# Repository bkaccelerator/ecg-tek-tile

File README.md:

# ecg-tek-tile
Biorhythm-sensing textile component.

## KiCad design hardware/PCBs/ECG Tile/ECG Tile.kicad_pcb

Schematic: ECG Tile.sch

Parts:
J1: Conn_01x03_Female; PinHeader_1x03_P2.54mm_Vertical
U1: Adafruit_Metro_Mini_328
U2: AD8232_Heart_Monitor_Sparkfun_Breakout

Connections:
+3V3: J1.3, U1.17, U2.2
GND: J1.1, U1.19, U1.20, U2.1
unnamed: J1.2, U1.6
unnamed: U1.3, U2.4
unnamed: U1.4, U2.5
unnamed: U1.23, U2.3

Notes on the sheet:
Neopixel Connection

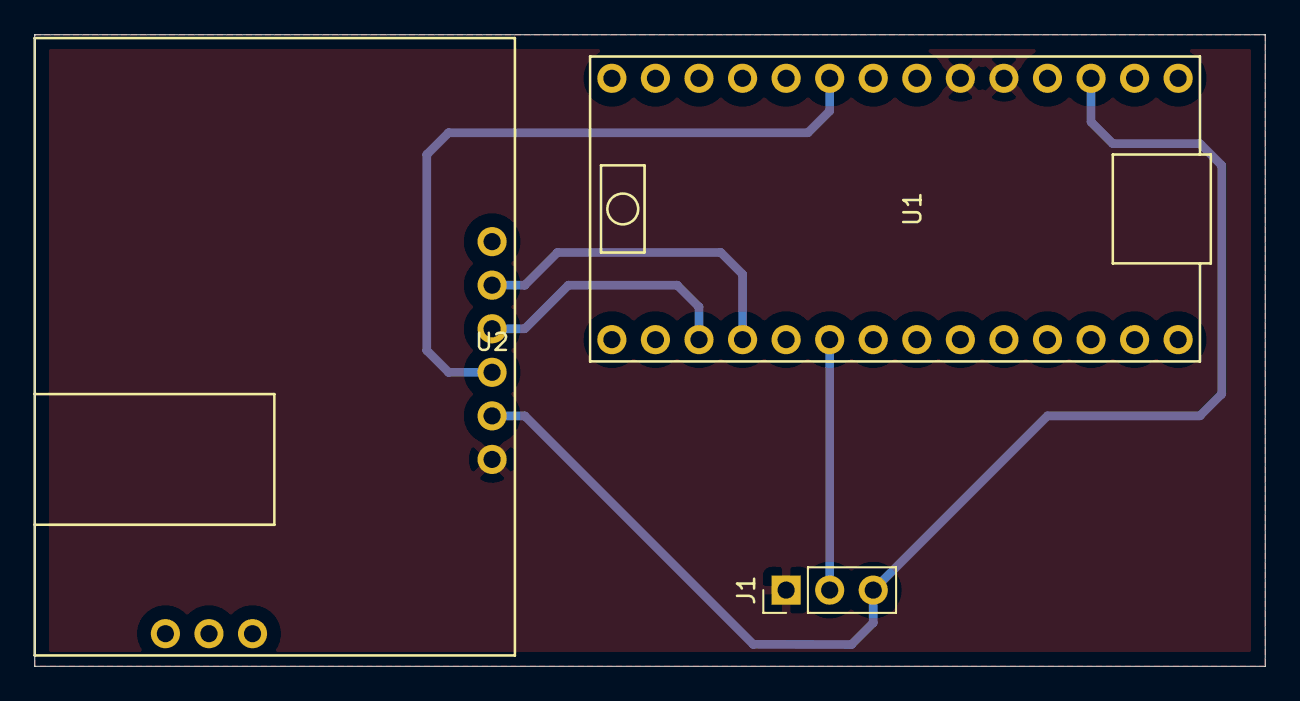
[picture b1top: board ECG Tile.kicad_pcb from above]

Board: 2 copper layers, 71.8 x 36.8 mm, 3 parts (0 on the bottom side), 6 nets.

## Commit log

2019-06-10 Snapshot
2019-06-10 Print raw sensor reading for Arduino Serial Plotter
2019-06-10 Just one LED
